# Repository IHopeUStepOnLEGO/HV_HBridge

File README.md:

# HV_HBridge

Kicad project for an high voltage h-bridge to produce an 300V AC square wave signal from given input pwm.

The used dc-dc regulator will transform a input voltage of 0 - 12V linearly up to 0-300V. 

Since the dc-dc regulator can deliver up to 1W max, the current will not exceed 3.33mA in 300V application.

This project was used to test the dielectric hold force between the plates of an variable capacitor.

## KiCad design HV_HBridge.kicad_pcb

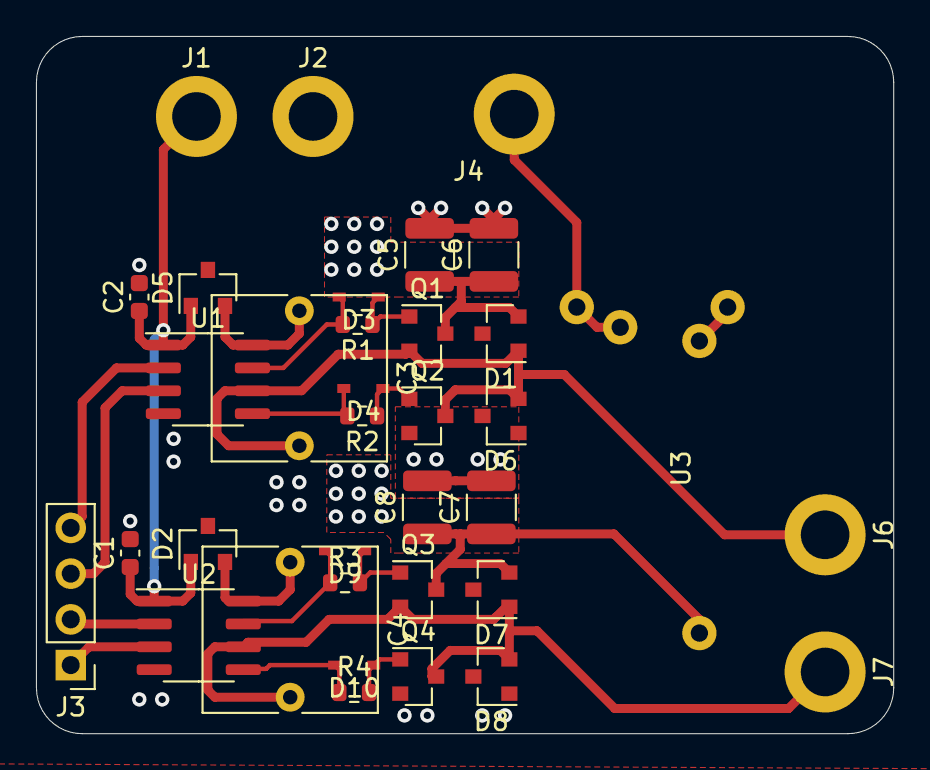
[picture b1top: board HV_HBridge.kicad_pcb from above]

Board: 2 copper layers, 47.6 x 38.7 mm, 35 parts (0 on the bottom side), 20 nets.

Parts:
C1, C2: 100n 25V; C_0603_1608Metric
C3, C4: 1u 630V; C_Rect_L9.0mm_W9.5mm_P7.50mm_MKT
C5, C6, C7, C8: 100n 630V; C_1210_3225Metric
D1, D2, D5, D6, D7, D8: BAS101; SOT-23
D3, D4, D9, D10: D; SOD-323
J1, J2, J4, J6, J7: Conn_01x01_Male; MountingHole_2.7mm_M2.5_ISO7380_Pad
J3: Conn_01x04; PinHeader_1x04_P2.54mm_Vertical
Q1, Q2, Q3, Q4: BSS127; SOT-23
R1, R2, R3, R4: 27R 50V; R_0603_1608Metric
U1, U2: IR2104; SOIC-8_3.9x4.9mm_P1.27mm
U3: A03P-12

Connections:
/hbridge1/LOAD1: C3.2, D1.1, D6.2, J6.1, Q1.2, Q2.3, U1.6
/hbridge1/LOAD2: C4.2, D7.1, D8.2, J7.1, Q3.2, Q4.3, U2.6
/hbridge1/PWM1: J3.4, U1.2
/hbridge1/PWM1_EN: J3.3, U1.3
/hbridge1/PWM2: J3.2, U2.2
/hbridge1/PWM2_EN: J3.1, U2.3
GND: C1.2, C2.2, C5.2, C6.2, C7.2, C8.2, D6.1, D8.1, J2.1, Q2.2, Q4.2, U1.4, U2.4, U3.1, U3.4
HS_A: D3.1, R1.2, U1.7
HS_B: D9.1, R3.1, U2.7
LS_A: D4.1, R2.2, U1.5
LS_B: D10.1, R4.1, U2.5
unnamed: C3.1, D5.2, U1.8
unnamed: C4.1, D2.2, U2.8
unnamed: D3.2, Q1.1, R1.1
unnamed: D4.2, Q2.1, R2.1
unnamed: D9.2, Q3.1, R3.2
unnamed: D10.2, Q4.1, R4.2
VCC: C5.1, C6.1, C7.1, C8.1, D1.2, D7.2, Q1.3, Q3.3, U3.3
VDD: C1.1, C2.1, D2.1, D5.1, J1.1, U1.1, U2.1
V_Var: J4.1, U3.2, U3.5

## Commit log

2021-08-19 first update
2021-09-24 updated to latest version
2021-09-24 changed board fsilk to 'HV_HBridge'
